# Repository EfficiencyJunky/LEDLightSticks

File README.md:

# LEDLightSticks
A standalone light fixture that you can also wear

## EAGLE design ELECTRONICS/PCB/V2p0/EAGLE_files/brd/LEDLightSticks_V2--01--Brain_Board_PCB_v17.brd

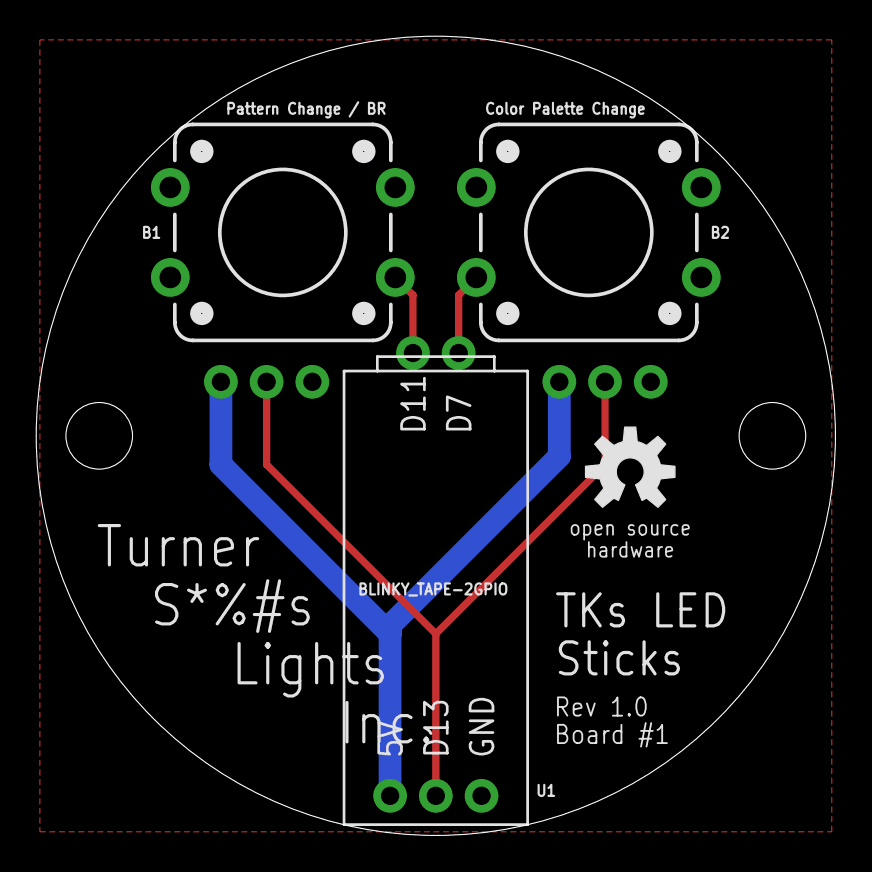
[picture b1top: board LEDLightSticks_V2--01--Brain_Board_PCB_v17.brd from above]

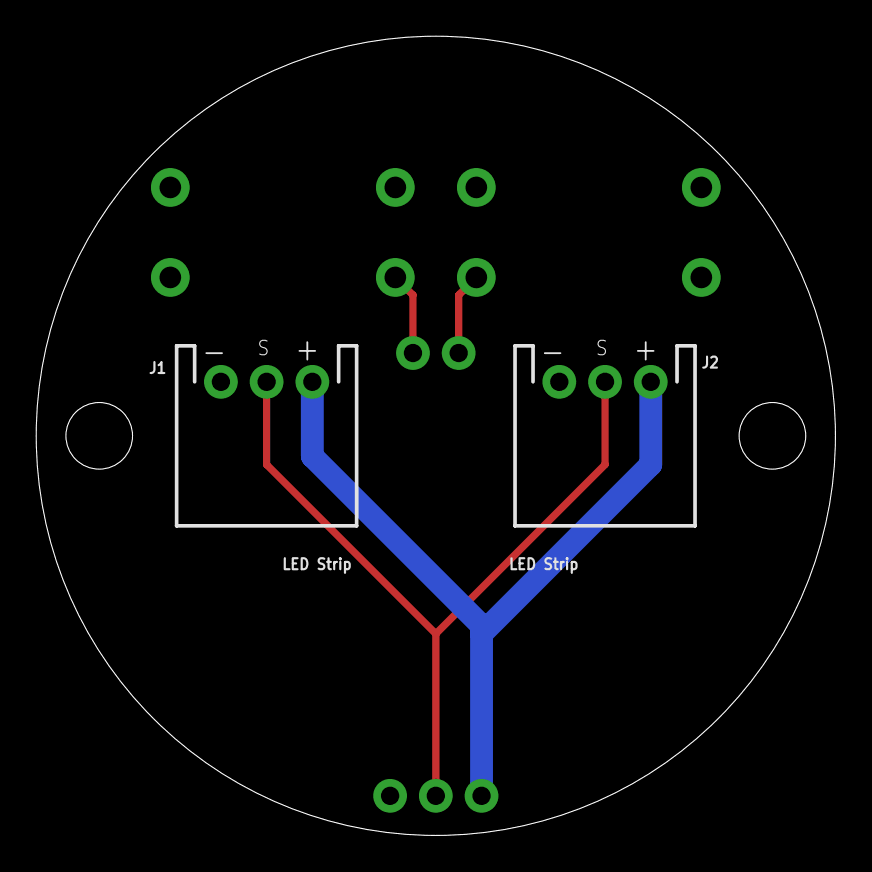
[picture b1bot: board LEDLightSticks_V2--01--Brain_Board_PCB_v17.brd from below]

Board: 2 copper layers, 44.4 x 44.4 mm, 6 parts (2 on the bottom side), 5 nets.

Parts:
B1: Pattern Change / BR; TACTILE_SWITCH_PTH_12MM
B2: Color Palette Change; TACTILE_SWITCH_PTH_12MM
J1, J2: LED Strip; JST-3-PTH-XH-RA
LOGO1: OSHW-LOGOM; OSHW-LOGO-M
U1: BLINKY_TAPE-2GPIO

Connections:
GND: B1.3, B2.1, J1.GND, J2.GND, U1.GND
unnamed: J1.SIGNAL, J2.SIGNAL, U1.SIGNAL
unnamed: B1.1, U1.D11
unnamed: B2.3, U1.D7
VIN: J1.5V, J2.5V, U1.5V

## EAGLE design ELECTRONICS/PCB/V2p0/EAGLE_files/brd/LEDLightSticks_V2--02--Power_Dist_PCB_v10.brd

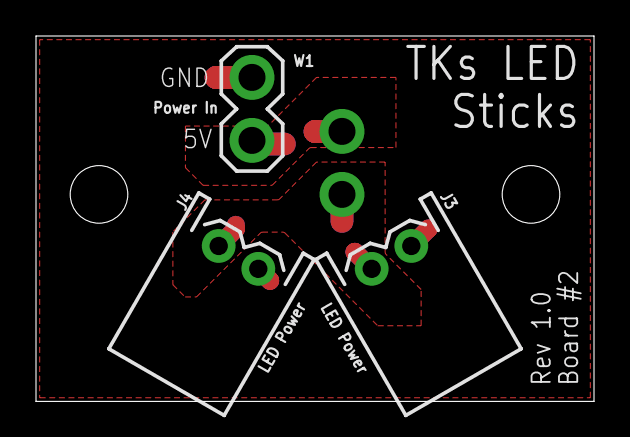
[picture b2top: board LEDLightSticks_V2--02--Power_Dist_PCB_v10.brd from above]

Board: 2 copper layers, 31.0 x 20.3 mm, 4 parts (1 on the bottom side), 3 nets.

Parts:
J3, J4: LED Power; JST-2-PTH-XH-RA
S1: On/Off Switch; 1X02_1.5MM
W1: Power In; 1X02_1.5MM

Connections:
GND: J3.1, J4.1, W1.2
VCC: J3.2, J4.2, S1.1
VIN: S1.2, W1.1

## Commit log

2020-11-02 finished V1p0 of Electronics Designs
2020-11-04 added some enclosure 3d models
2020-12-22 Added some 3D Models and started working on code
2020-12-22 finished initial main ino sketch structure
2020-12-23 Finished initial structure of LEDStripController Class
2020-12-23 tested and fixed some minor "warning" type issues in class implementation
2020-12-23 Cleaned up code and implemented splitting single CRGB array across many controllers
2020-12-23 added ability to split one physical strip into multiple virtual strips and color palettes
2020-12-25 added ability to create array of animations to cycle through
2020-12-25 added fill_palette for rainbow, speed control, and fixed issues
2020-12-27 added speed control and tweaked all current animations
2020-12-27 finished tweaking palette animation speed settings
2020-12-28 added new .ino file that prepares EEPROM to store settings
2020-12-28 added saving settings to EEPROM
2020-12-28 added all animations, cycle, and solid color
2020-12-29 added colorwaves() animation and started adding a TON of gradient palettes
2020-12-30 implemented color palettes into core animations
2020-12-31 now using settings struct to manage and update settings
2020-12-31 setup initializations for all animations and moved static variables to class
2020-12-31 added longpress of secondary button to show/scroll palettes and fixed colorwaves bugs
2020-12-31 fixed issue when in SHOW_PALETTE mode with SOLID_COLOR animation
2020-12-31 got a good start on devin animation
2020-12-31 added ability to turn LED strip off when there's no off button
2021-01-02 Cleaned up code A LOT and added Pride animation
2021-01-02 fixed a minor issue and replaced A_RAINBOW with A_PALETTE
2021-01-02 added random number seed to initialize random colorwave palette
2021-01-05 added ability to address each strip individually. updated code/pcb1
2021-01-05 removed all gcodes
2021-01-05 actually ignored all gcodes
2021-01-05 FINALLY ignored gcodes
2021-01-05 removed gcodes
2021-01-05 restructured directory
2021-01-06 One more pass of arduino code PRODUCTION READY!!! (and added Bottom Main STL)
2021-01-07 Updated all 3D Models to use 4M mounting hardware
2021-01-09 added M4 Enclosure STLs and 3MF files
2021-01-09 updated power shim casing to fit snuggly with Molex 1.5A USB plug
2021-01-09 Updated build instructions
2021-01-10 added pcb cover in base and Storage container for power Shim
2021-01-16 Reorganized all 3D Model files and streamlined naming conventions
2021-01-19 Updated all 3mf files and STLs to version 123
2021-02-15 Updated a bunch of 3D Models
2021-02-16 finished updating all 3d models and 3MF files to latest
2021-02-16 removed 3D Model files for 10_32 hardware version
2021-02-16 added STL files
2021-03-30 updated enclosure
2021-03-30 added hasonoffswitch boolean to teensy
2024-03-03 updated hardware defs to include Trinket Pro and added latest 3D Print Files
2024-06-22 Update README.md
    started adding hyperlinks in TOC
2024-06-22 Update README.md
    added all hyper links to TOC
2024-06-23 Update README.md to include 3D Model files
2024-06-23 Update README.md added power shim case 3d models
2024-07-02 added photos for step 01 and step 02
2024-07-02 Update README.md
    added images to step 01
2024-07-10 added VR Headset definitions
2024-07-22 Update README.md to show pictures for step 2
